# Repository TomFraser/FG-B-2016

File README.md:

# FG&B 2016 Repo
-------------------------------------------------------------

**Feel Free To Use Any Concepts Used Within This Repo.**
**If You Plan On Copying Large Parts Of Code, Please Email tr.fraser@bigpond.com For Permission**

-------------------------------------------------------------

**SHF Robotics**

Main Repo for FG&B Robotics (Formerly SHF Robotics) 2016

Tom Hulbert, Tom Fraser, Alistair English, William Plummer, Cooper Richmond :heart::heart:

-------------------------------------------------------------

To Do List
- [x] Make Robot
- [x] Make Robot Work
- [x] Watch Robot Fail at Nationals Because of the **curse**
- ^^^^ IT REALLY HAPPENED!

-------------------------------------------------------------

Sorry about rude commit messages, comments and messy code.

-------------------------------------------------------------

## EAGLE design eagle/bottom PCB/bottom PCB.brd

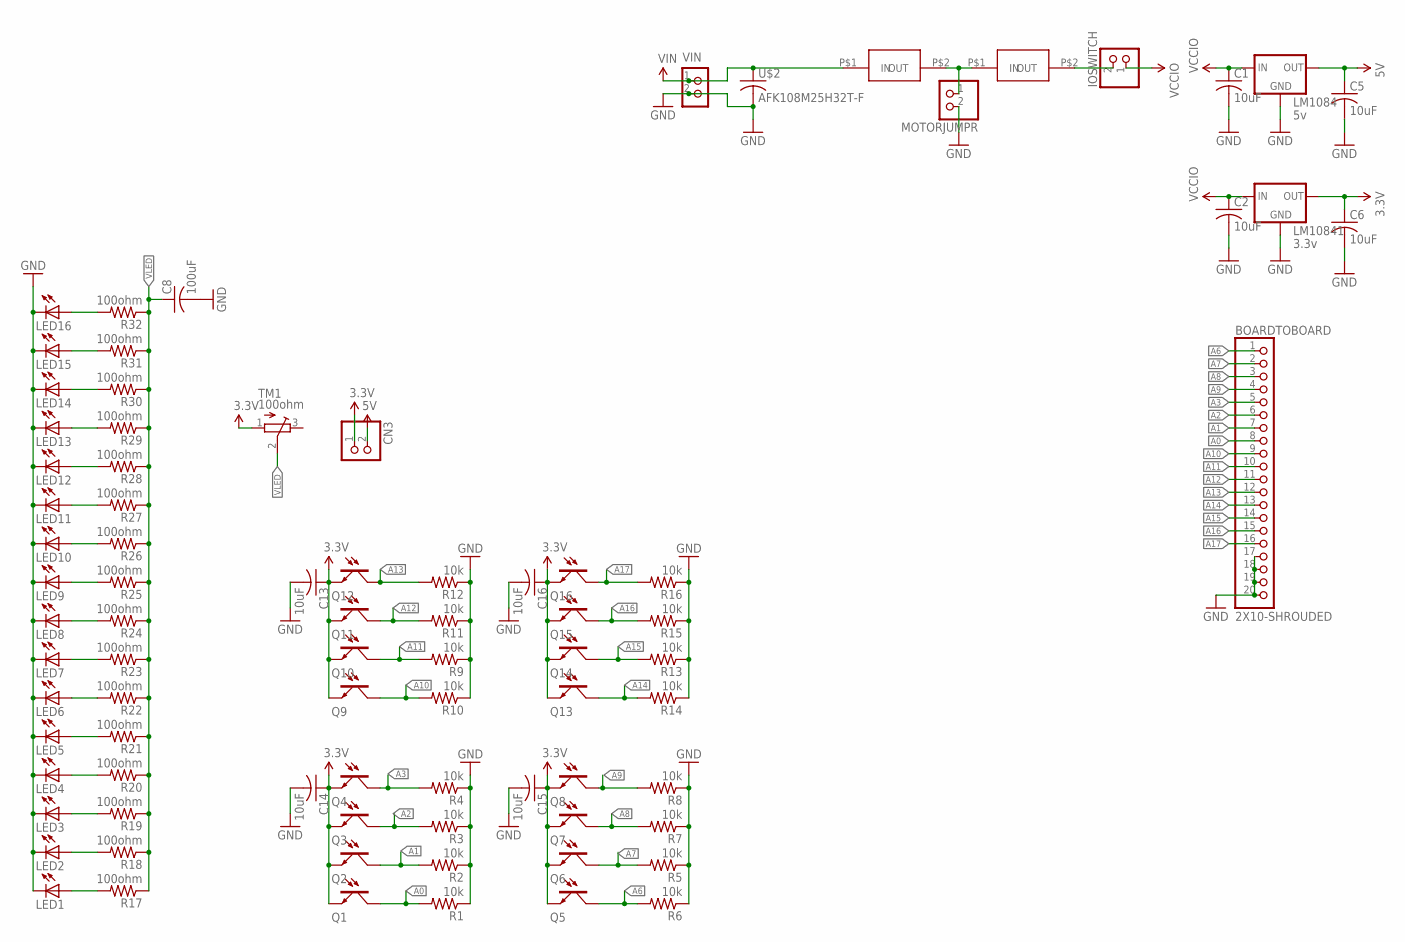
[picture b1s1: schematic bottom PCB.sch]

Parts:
2A: 0153007_FUSE; 0153007_
5A: 5a; 0153007_
BOARDTOBOARD: 2X10-SHROUDED
C1, C2, C5, C6, C13, C14, C15, C16: 10uF; C0805
C8: 100uF; C0805
CN3: JST_2PIN-SMT; JST-PH-2-SMT
IOSWITCH: JST_2PIN-SMT; JST-PH-2-SMT
LED1, LED2, LED3, LED4, LED5, LED6, LED7, LED8, LED9, LED10, LED11, LED12, LED13, LED14, LED15, LED16: LEDCHIPLED_0805; CHIPLED_0805
LM1084: 5v; D2PACK
LM10841: 3.3v; D2PACK
MOTORJUMPR: JST_2PIN-SMT; JST-PH-2-SMT
Q1, Q2, Q3, Q4, Q5, Q6, Q7, Q8, Q9, Q10, Q11, Q12, Q13, Q14, Q15, Q16: PHOTOTRANSISTORCHIPLED_1206; CHIPLED_1206
R1, R2, R3, R4, R5, R6, R7, R8, R9, R10, R11, R12, R13, R14, R15, R16: 10k; M0805
R17, R18, R19, R20, R21, R22, R23, R24, R25, R26, R27, R28, R29, R30, R31, R32: 100ohm; M0805
TM1: 100ohm; TC33X
U$2: AFK108M25H32T-F
VIN: CON_TERMINAL_BLOCK_02-5MM; TERMINAL_BLOCK_2P_5

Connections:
3.3V: C6.1, C13.1, C14.1, C15.1, C16.1, CN3.1 (2), LM10841.2 (VOUT), Q1.C, Q2.C, Q3.C, Q4.C, Q5.C, Q6.C, Q7.C, Q8.C, Q9.C, Q10.C, Q11.C, Q12.C, Q13.C, Q14.C, Q15.C, Q16.C, TM1.1 (A)
5V: C5.1, CN3.2 (1), LM1084.2 (VOUT)
A0: BOARDTOBOARD.8, Q1.A, R1.2
A1: BOARDTOBOARD.7, Q2.A, R2.2
A2: BOARDTOBOARD.6, Q3.A, R3.2
A3: BOARDTOBOARD.5, Q4.A, R4.2
A6: BOARDTOBOARD.1, Q5.A, R6.2
A7: BOARDTOBOARD.2, Q6.A, R5.2
A8: BOARDTOBOARD.3, Q7.A, R7.2
A9: BOARDTOBOARD.4, Q8.A, R8.2
A10: BOARDTOBOARD.9, Q9.A, R10.2
A11: BOARDTOBOARD.10, Q10.A, R9.2
A12: BOARDTOBOARD.11, Q11.A, R11.2
A13: BOARDTOBOARD.12, Q12.A, R12.2
A14: BOARDTOBOARD.13, Q13.A, R14.2
A15: BOARDTOBOARD.14, Q14.A, R13.2
A16: BOARDTOBOARD.15, Q15.A, R15.2
A17: BOARDTOBOARD.16, Q16.A, R16.2
GND: BOARDTOBOARD.17, BOARDTOBOARD.18, BOARDTOBOARD.19, BOARDTOBOARD.20, C1.2, C2.2, C5.2, C6.2, C8.2, C13.2, C14.2, C15.2, C16.2, LED1.C, LED2.C, LED3.C, LED4.C, LED5.C, LED6.C, LED7.C, LED8.C, LED9.C, LED10.C, LED11.C, LED12.C, LED13.C, LED14.C, LED15.C, LED16.C, LM1084.1 (GND), LM10841.1 (GND), MOTORJUMPR.2 (1), R1.1, R2.1, R3.1, R4.1, R5.1, R6.1, R7.1, R8.1, R9.1, R10.1, R11.1, R12.1, R13.1, R14.1, R15.1, R16.1, U$2.POS (2), VIN.2
unnamed: LED1.A, R17.2
unnamed: 2A.P$2 (OUT), IOSWITCH.2 (1)
unnamed: LED2.A, R18.2
unnamed: LED3.A, R19.2
unnamed: LED4.A, R20.2
unnamed: LED5.A, R21.2
unnamed: LED6.A, R22.2
unnamed: LED7.A, R23.2
unnamed: LED8.A, R24.2
unnamed: LED9.A, R25.2
unnamed: LED10.A, R26.2
unnamed: LED11.A, R27.2
unnamed: LED12.A, R28.2
unnamed: LED13.A, R29.2
unnamed: LED14.A, R30.2
unnamed: LED15.A, R31.2
unnamed: LED16.A, R32.2
VCC: 2A.P$1 (IN), 5A.P$2 (OUT), MOTORJUMPR.1 (2)
VCCIO: C1.1, C2.1, IOSWITCH.1 (2), LM1084.3 (VIN), LM10841.3 (VIN)
VIN: 5A.P$1 (IN), U$2.NEG (1), VIN.1
VLED: C8.1, R17.1, R18.1, R19.1, R20.1, R21.1, R22.1, R23.1, R24.1, R25.1, R26.1, R27.1, R28.1, R29.1, R30.1, R31.1, R32.1, TM1.2 (S)

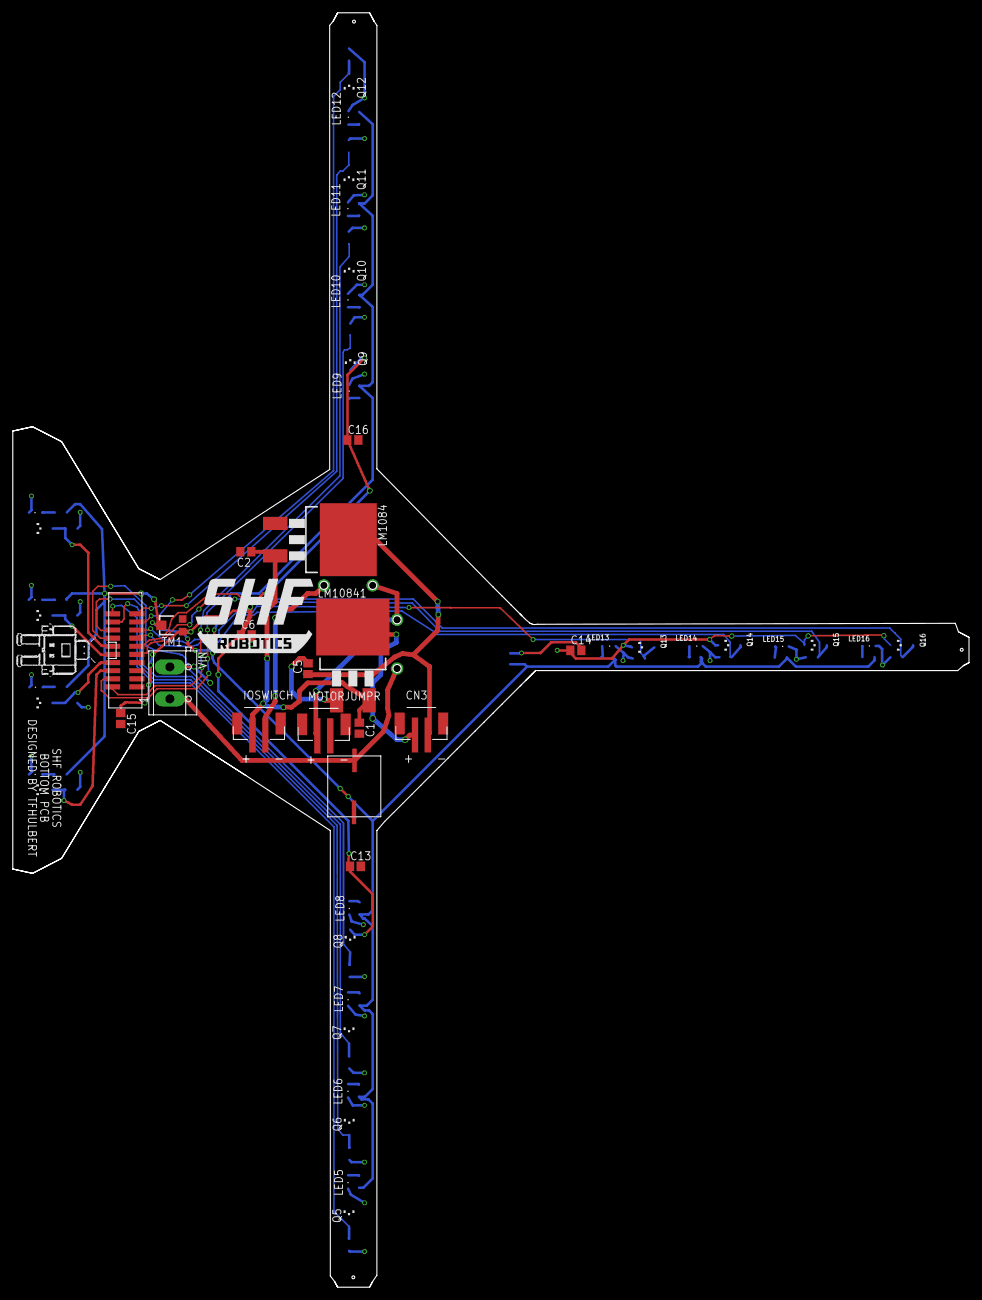
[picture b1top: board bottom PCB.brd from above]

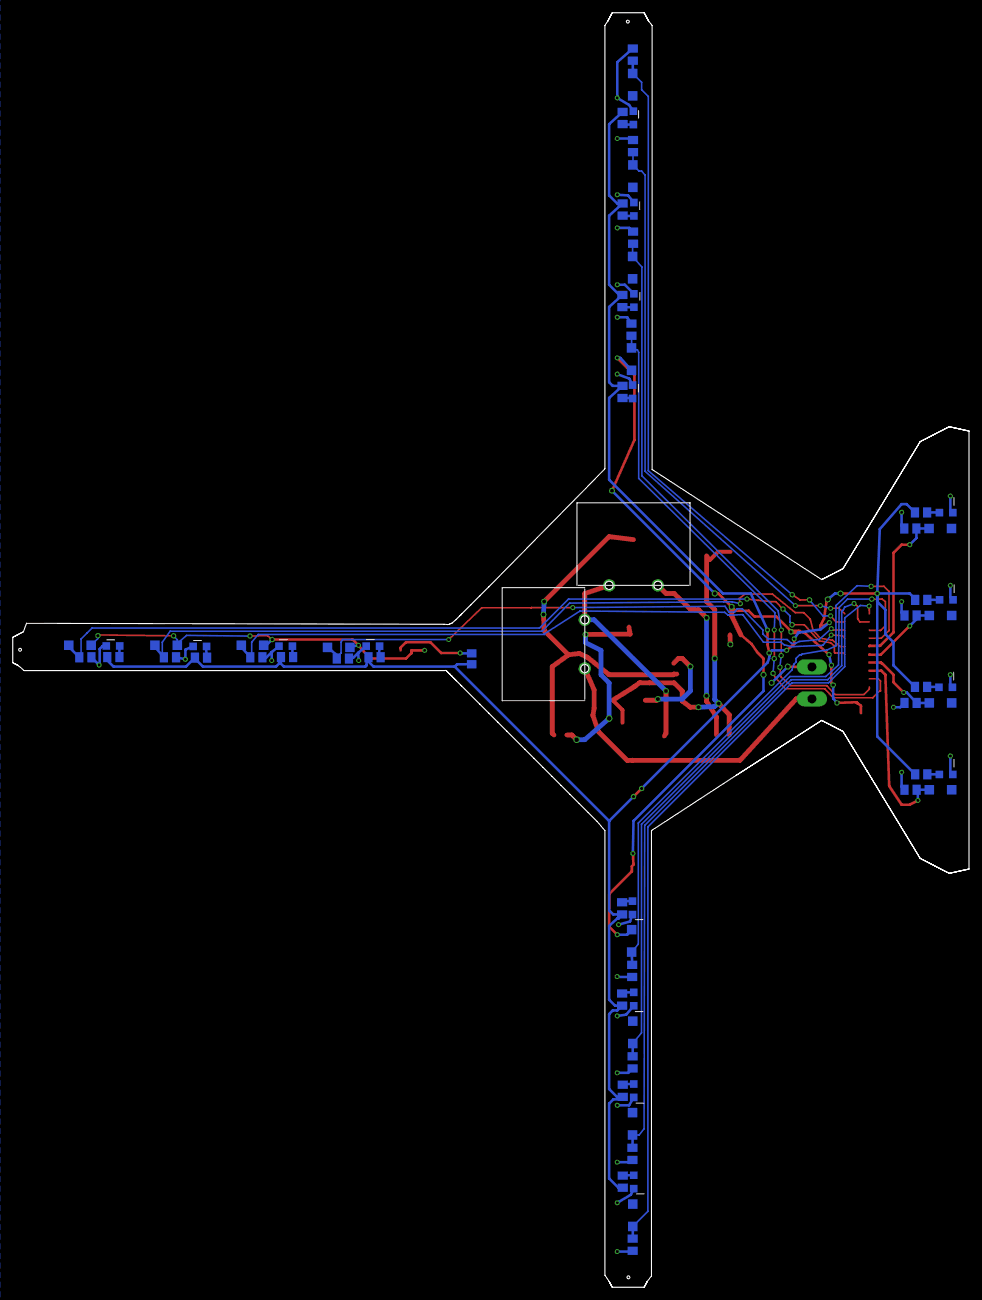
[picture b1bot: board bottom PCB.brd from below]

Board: 2 copper layers, 149.5 x 199.2 mm, 84 parts (35 on the bottom side), 40 nets.

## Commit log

2017-02-21 inital Commit from private repo
2017-02-27 Fixed Readme
2018-04-12 Updated readme to be public

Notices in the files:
parts and their libraries:
SparkFun-Aesthetics: Licensing: Creative Commons ShareAlike 4.0 International - https://creativecommons.org/licenses/by-sa/4.0
